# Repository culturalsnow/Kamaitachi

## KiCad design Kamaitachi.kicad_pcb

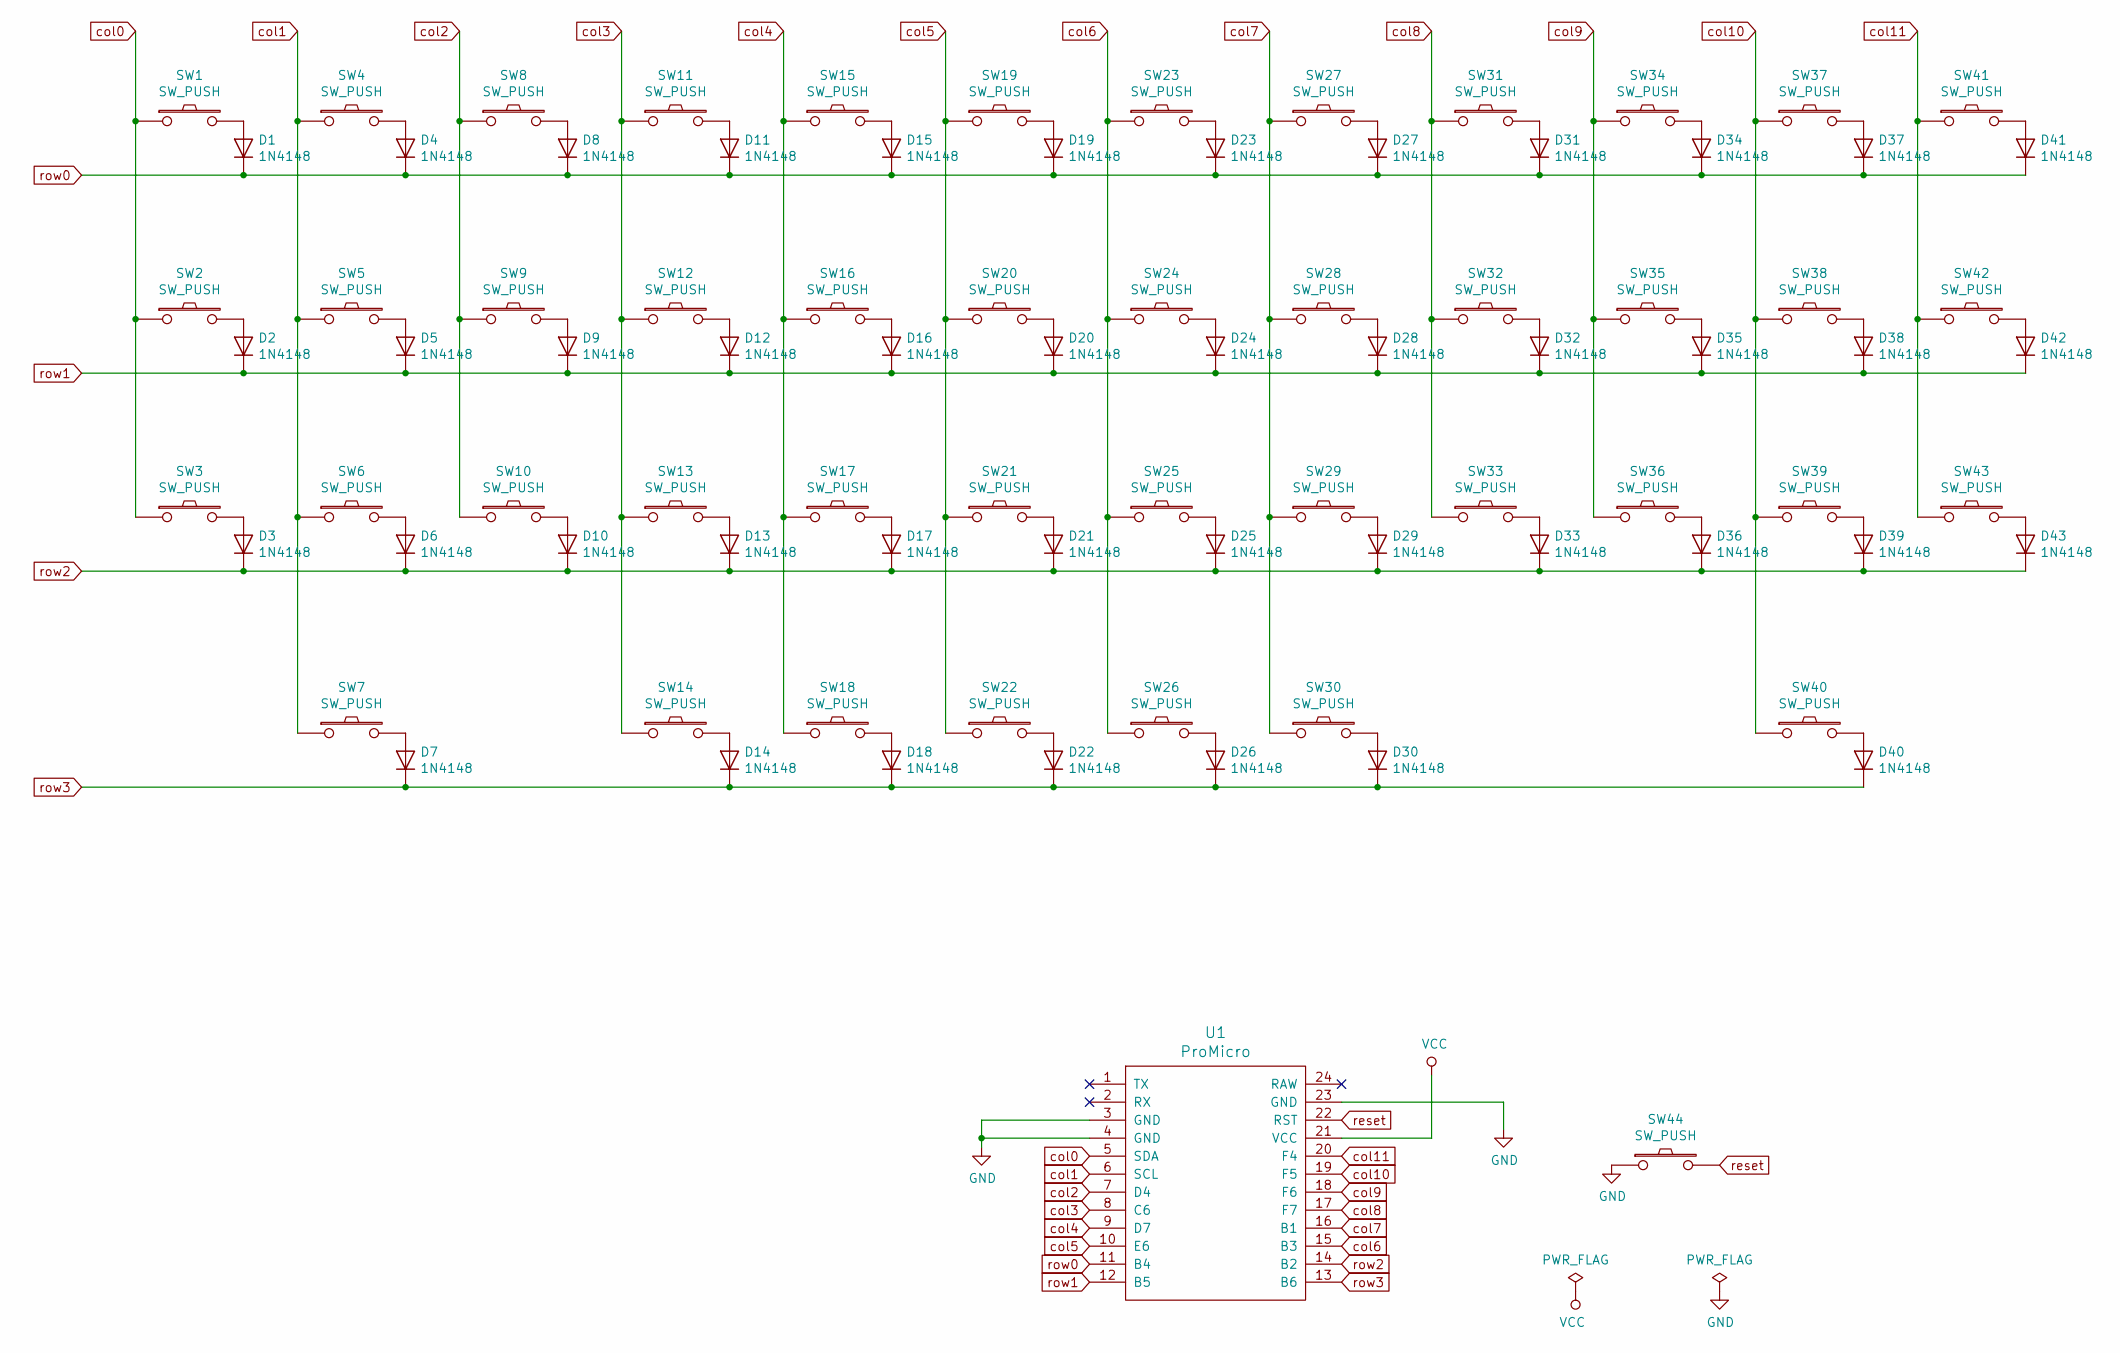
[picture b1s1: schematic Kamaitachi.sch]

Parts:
D1, D2, D3, D4, D5, D6, D7, D8, D9, D10, D11, D12, D13, D14, D15, D16, D17, D18, D19, D20, D21, D22, D23, D24, D25, D26, D27, D28, D29, D30, D31, D32, D33, D34, D35, D36, D37, D38, D39, D40, D41, D42, D43: 1N4148; D_SOD-123
SW1, SW2, SW3, SW4, SW5, SW6, SW8, SW9, SW10, SW11, SW12, SW13, SW14, SW15, SW16, SW17, SW19, SW20, SW21, SW22, SW23, SW24, SW25, SW27, SW28, SW29, SW30, SW31, SW32, SW33, SW34, SW35, SW36, SW37, SW38, SW39, SW41, SW42, SW43: SW_PUSH; MX_PCB_100H
SW7, SW40: SW_PUSH; MX_PCB_150H
SW18, SW26: SW_PUSH; MX_PCB_125H
SW44: SW_PUSH; ResetSW
U1: ProMicro; ProMicro_v2_Backside

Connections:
GND: SW44.1, U1.3 (GND), U1.4 (GND), U1.23 (GND)
unnamed: D1.2 (A), SW1.2
unnamed: D2.2 (A), SW2.2
unnamed: D3.2 (A), SW3.2
unnamed: D4.2 (A), SW4.2
unnamed: D5.2 (A), SW5.2
unnamed: D6.2 (A), SW6.2
unnamed: D7.2 (A), SW7.2
unnamed: D8.2 (A), SW8.2
unnamed: D9.2 (A), SW9.2
unnamed: D10.2 (A), SW10.2
unnamed: D11.2 (A), SW11.2
unnamed: D12.2 (A), SW12.2
unnamed: D13.2 (A), SW13.2
unnamed: D14.2 (A), SW14.2
unnamed: D15.2 (A), SW15.2
unnamed: D16.2 (A), SW16.2
unnamed: D17.2 (A), SW17.2
unnamed: D18.2 (A), SW18.2
unnamed: D19.2 (A), SW19.2
unnamed: D20.2 (A), SW20.2
unnamed: D21.2 (A), SW21.2
unnamed: D22.2 (A), SW22.2
unnamed: D23.2 (A), SW23.2
unnamed: D24.2 (A), SW24.2
unnamed: D25.2 (A), SW25.2
unnamed: D26.2 (A), SW26.2
unnamed: D27.2 (A), SW27.2
unnamed: D28.2 (A), SW28.2
unnamed: D29.2 (A), SW29.2
unnamed: D30.2 (A), SW30.2
unnamed: D31.2 (A), SW31.2
unnamed: D32.2 (A), SW32.2
unnamed: D33.2 (A), SW33.2
unnamed: D34.2 (A), SW34.2
unnamed: D35.2 (A), SW35.2
unnamed: D36.2 (A), SW36.2
unnamed: D37.2 (A), SW37.2
unnamed: D38.2 (A), SW38.2
unnamed: D39.2 (A), SW39.2
unnamed: D40.2 (A), SW40.2
unnamed: D41.2 (A), SW41.2
unnamed: D42.2 (A), SW42.2
unnamed: D43.2 (A), SW43.2
VCC: U1.21 (VCC)
col0: SW1.1, SW2.1, SW3.1, U1.5 (SDA)
col1: SW4.1, SW5.1, SW6.1, SW7.1, U1.6 (SCL)
col2: SW8.1, SW9.1, SW10.1, U1.7 (D4)
col3: SW11.1, SW12.1, SW13.1, SW14.1, U1.8 (C6)
col4: SW15.1, SW16.1, SW17.1, SW18.1, U1.9 (D7)
col5: SW19.1, SW20.1, SW21.1, SW22.1, U1.10 (E6)
col6: SW23.1, SW24.1, SW25.1, SW26.1, U1.15 (B3)
col7: SW27.1, SW28.1, SW29.1, SW30.1, U1.16 (B1)
col8: SW31.1, SW32.1, SW33.1, U1.17 (F7)
col9: SW34.1, SW35.1, SW36.1, U1.18 (F6)
col10: SW37.1, SW38.1, SW39.1, SW40.1, U1.19 (F5)
col11: SW41.1, SW42.1, SW43.1, U1.20 (F4)
reset: SW44.2, U1.22 (RST)
row0: D1.1 (K), D4.1 (K), D8.1 (K), D11.1 (K), D15.1 (K), D19.1 (K), D23.1 (K), D27.1 (K), D31.1 (K), D34.1 (K), D37.1 (K), D41.1 (K), U1.11 (B4)
row1: D2.1 (K), D5.1 (K), D9.1 (K), D12.1 (K), D16.1 (K), D20.1 (K), D24.1 (K), D28.1 (K), D32.1 (K), D35.1 (K), D38.1 (K), D42.1 (K), U1.12 (B5)
row2: D3.1 (K), D6.1 (K), D10.1 (K), D13.1 (K), D17.1 (K), D21.1 (K), D25.1 (K), D29.1 (K), D33.1 (K), D36.1 (K), D39.1 (K), D43.1 (K), U1.14 (B2)
row3: D7.1 (K), D14.1 (K), D18.1 (K), D22.1 (K), D26.1 (K), D30.1 (K), D40.1 (K), U1.13 (B6)

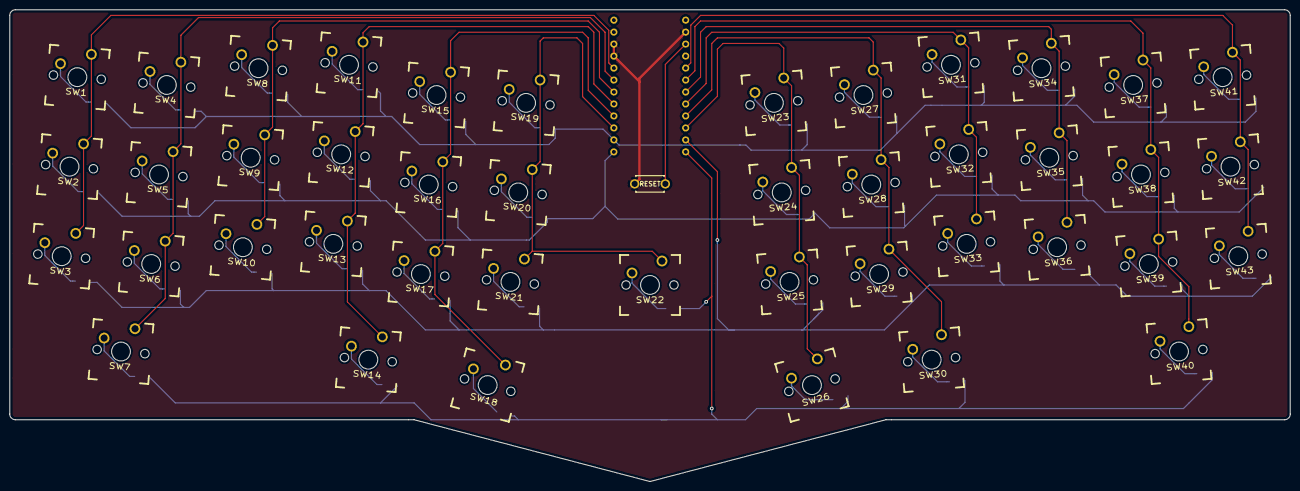
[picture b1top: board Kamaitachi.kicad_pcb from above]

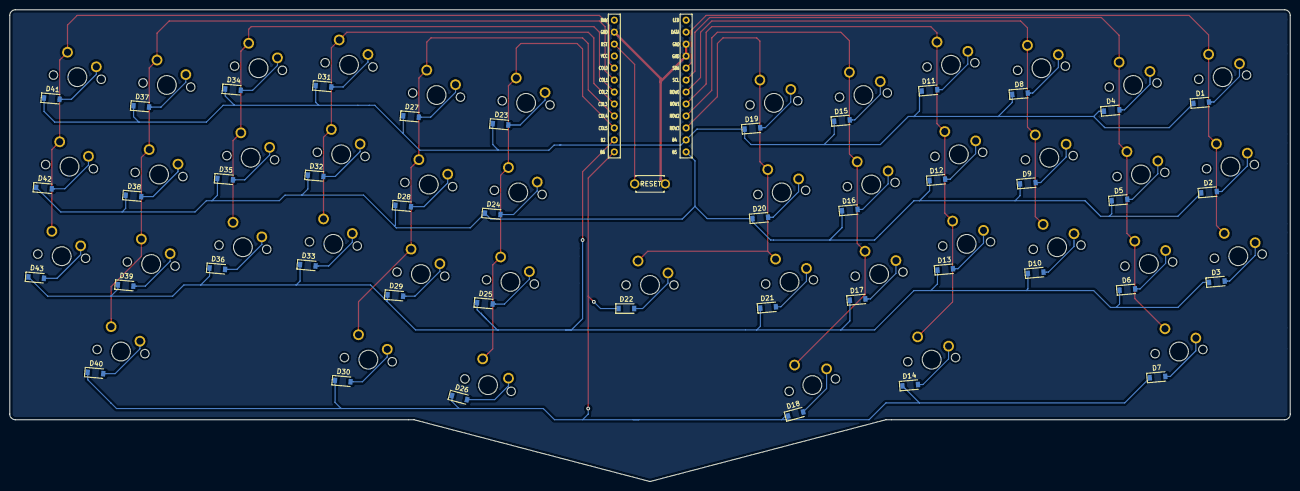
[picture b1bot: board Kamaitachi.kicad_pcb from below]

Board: 2 copper layers, 271.5 x 100.0 mm, 88 parts (44 on the bottom side), 61 nets.

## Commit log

2019-06-02 pcb in progress
2019-06-05 pcb finished
2019-06-08 weekend additions
2019-06-27 plates and pcb finished
